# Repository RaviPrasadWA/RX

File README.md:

# RX
NRF based reciever with FHSS ( aka AFHDS )

3D models on : https://grabcad.com/library/rx-case-2

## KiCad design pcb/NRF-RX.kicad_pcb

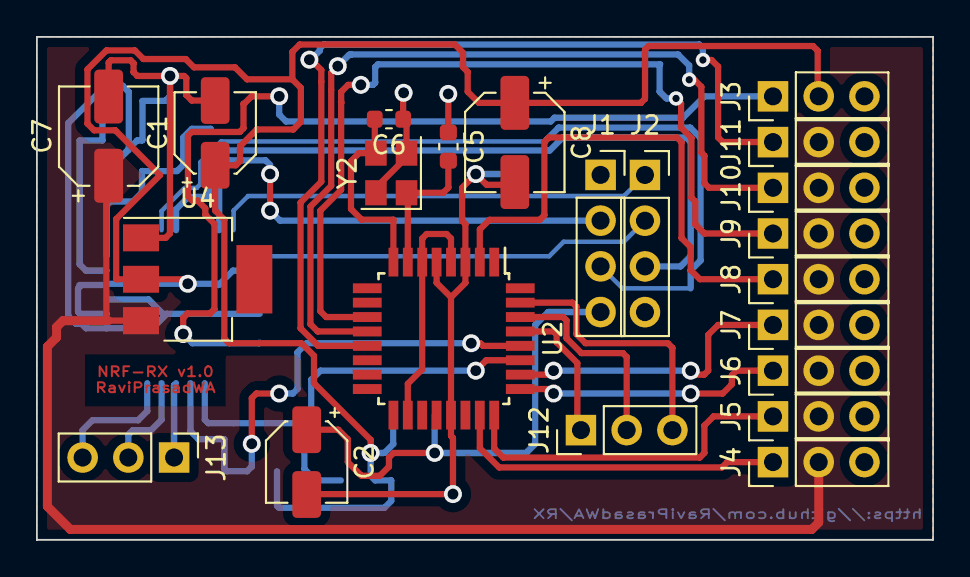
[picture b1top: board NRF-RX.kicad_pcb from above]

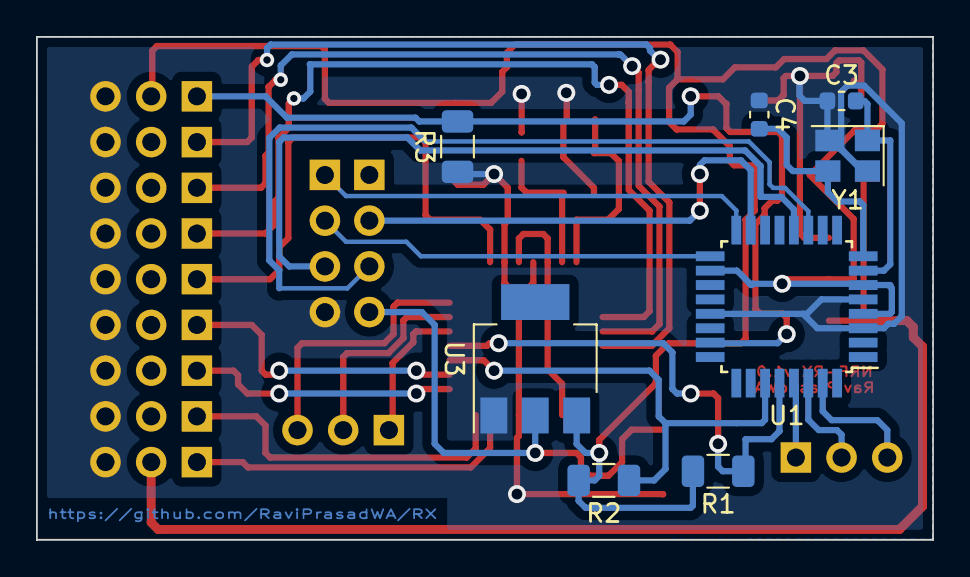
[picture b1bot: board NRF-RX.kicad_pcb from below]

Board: 2 copper layers, 49.8 x 27.9 mm, 30 parts (8 on the bottom side), 30 nets.

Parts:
C1, C2: CP; CP_Elec_4x5.7
C3, C4, C5, C6: 16pF; C_0603_1608Metric
C7, C8: CP; CP_Elec_5x5.4
J1, J2: Conn_01x04_Female; PinSocket_1x04_P2.54mm_Vertical
J3: BIND; PinHeader_1x03_P2.54mm_Vertical
J4: CH1; PinHeader_1x03_P2.54mm_Vertical
J5: CH2; PinHeader_1x03_P2.54mm_Vertical
J6: CH3; PinHeader_1x03_P2.54mm_Vertical
J7, J12, J13: CH4; PinHeader_1x03_P2.54mm_Vertical
J8: CH5; PinHeader_1x03_P2.54mm_Vertical
J9: CH6; PinHeader_1x03_P2.54mm_Vertical
J10: CH7; PinHeader_1x03_P2.54mm_Vertical
J11: CH8; PinHeader_1x03_P2.54mm_Vertical
R1, R2: 2.2k; R_1206_3216Metric
R3: 10k; R_1206_3216Metric
U1, U2: ATmega328-AU; TQFP-32_7x7mm_P0.8mm
U3: LM1117-3.3; SOT-223
U4: LM1117-5.0; SOT-223
Y1, Y2: Crystal; Crystal_SMD_3225-4Pin_3.2x2.5mm

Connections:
+5V: C7.1, J4.2, J5.2, J6.2, J7.2, J8.2, J9.2, J10.2, J11.2, U4.3
GND: C1.2, C2.2, C3.1, C4.1, C5.1, C6.1, C7.2, C8.2, J2.4, J3.3, J4.3, J5.3, J6.3, J7.3, J8.3, J9.3, J10.3, J11.3, R3.1, U1.3, U1.5, U1.21, U2.3, U2.5, U2.21, U3.1, U4.1, Y1.2, Y2.2, Y2.4
unnamed: C1.1, C8.1, J3.2, R1.2, R2.2, U1.4, U1.6, U1.18, U2.4, U2.6, U2.18, U3.3, U4.2
unnamed: C2.1, J1.4, U3.2
unnamed: C3.2, U1.7, Y1.1
unnamed: C4.2, U1.8, Y1.3
unnamed: C5.2, U2.7, Y2.1
unnamed: C6.2, U2.8, Y2.3
unnamed: J1.2, U1.15
unnamed: J1.3, U1.11
unnamed: J2.1, U1.16
unnamed: J2.2, U1.17
unnamed: J2.3, U1.12
unnamed: J3.1, R3.2, U1.23
unnamed: J4.1, U2.23
unnamed: J5.1, U2.24
unnamed: J6.1, U2.25
unnamed: J7.1, U2.26
unnamed: J8.1, U2.2
unnamed: J9.1, U2.11
unnamed: J10.1, U2.12
unnamed: J11.1, U2.13
unnamed: J12.1, U2.29
unnamed: J12.2, U2.30
unnamed: J12.3, U2.31
unnamed: J13.1, U1.29
unnamed: J13.2, U1.30
unnamed: J13.3, U1.31
unnamed: R1.1, U1.28, U2.28
unnamed: R2.1, U1.27, U2.27

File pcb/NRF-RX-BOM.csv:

"Id";"Designator";"Package";"Quantity";"Designation";"Supplier and ref";
1;"C1,C2";"CP_Elec_4x5.7";2;"CP";;;
2;"C3,C4,C5,C6";"C_0603_1608Metric";4;"16pF";;;
3;"J1,J2";"PinHeader_1x04_P2.54mm_Vertical";2;"Conn_01x04_Female";;;
4;"J3";"PinHeader_1x03_P2.54mm_Vertical";1;"BIND";;;
5;"J4";"PinHeader_1x03_P2.54mm_Vertical";1;"CH1";;;
6;"J5";"PinHeader_1x03_P2.54mm_Vertical";1;"CH2";;;
7;"J6";"PinHeader_1x03_P2.54mm_Vertical";1;"CH3";;;
8;"J7,J12,J13";"PinHeader_1x03_P2.54mm_Vertical";3;"CH4";;;
9;"J8";"PinHeader_1x03_P2.54mm_Vertical";1;"CH5";;;
10;"J9";"PinHeader_1x03_P2.54mm_Vertical";1;"CH6";;;
11;"J10";"PinHeader_1x03_P2.54mm_Vertical";1;"CH7";;;
12;"J11";"PinHeader_1x03_P2.54mm_Vertical";1;"CH8";;;
13;"R1,R2";"R_1206_3216Metric";2;"2.2k";;;
14;"R3";"R_1206_3216Metric";1;"10k";;;
15;"U1,U2";"TQFP-32_7x7mm_P0.8mm";2;"ATmega328-AU";;;
16;"U3";"SOT-223";1;"LM1117-3.3";;;
17;"Y1,Y2";"Crystal_SMD_3225-4Pin_3.2x2.5mm";2;"Crystal";;;

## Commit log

2020-10-07 first commit of the complete NRF RX code with FHSS
2020-10-07 removed the unwanted init function for the channels data TODO: add the arm functionality to the channels_rx
2020-10-09 added the pcb files for the device
2020-10-09 scaled the images
2020-10-10 added the updated PCB file for the calculated size
2020-10-12 addd te hardware case files for the device
2020-10-18 addedthe case files TODO: add the socket dome and top plate
2020-10-24 completed files for the case
2020-11-08 added the changes
2020-11-09 addedthe single peice assy for each late
2020-11-18 added the complete assy
2020-11-18 addedthe url to 3d
